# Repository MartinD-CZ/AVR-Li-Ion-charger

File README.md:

# AVR Li-Ion charger
*see the article [here](http://embedblog.eu/?p=392)*

ATtiny44-controlled buck converter with adjustable charging parameters (charging voltage & current, precharging voltage & current, min/max temperatures, ...). Everything is configurable via a serial port and stored in EEPROM.

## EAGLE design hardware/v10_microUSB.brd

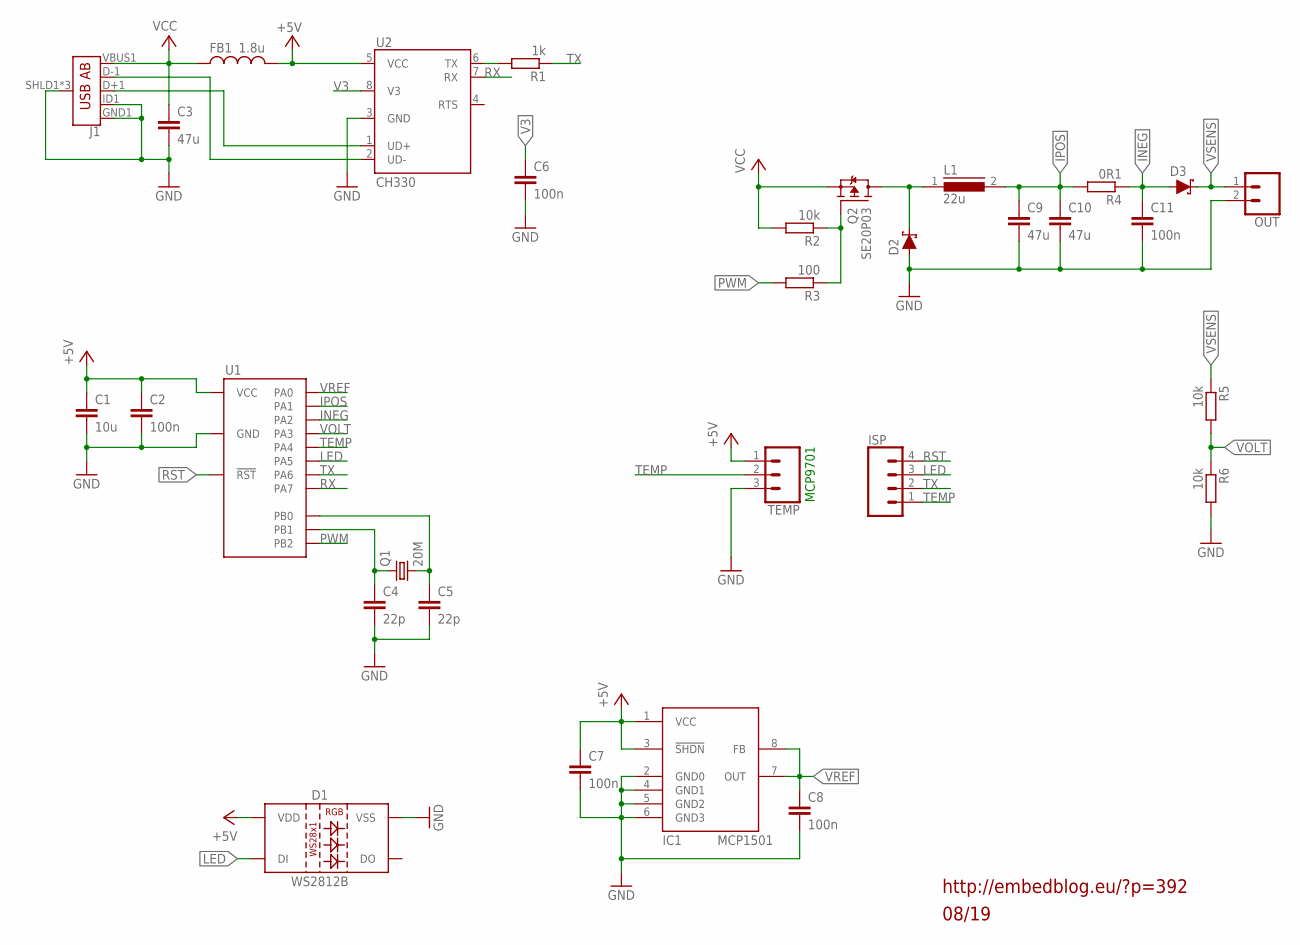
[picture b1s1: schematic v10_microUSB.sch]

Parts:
C1: 10u; C0805
C2, C6, C7, C8, C11: 100n; C0805
C3, C9, C10: 47u; C1206
C4, C5: 22p; C0805
D1: WS2812B
D2, D3: 3A/40V/500mV; SMA-DIODE
FB1: 1.8u; 1206
IC1: MCP1501; SO08
ISP: CONN_04; 1X04
J1: USB_AB_SMT; USB-AB-MICRO-SMD
L1: 22u; DR73
OUT: CONN_02PTH3; 1X02_LONGPADS
Q1: 20M; HC49/S
Q2: SE20P03; TO252
R1: 1k; R0805
R2, R5, R6: 10k; R0805
R3: 100; R0805
R4: 0R1; R1206
TEMP: 455-1750-1-ND; 1X03
U1: ATTINY24; SO014
U2: CH330; SO08

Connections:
+5V: C1.1, C2.1, C7.1, D1.1 (VDD), FB1.2, IC1.1 (VCC), IC1.3 (!SHDN), TEMP.1, U1.1 (VCC), U2.5 (VCC)
GND: C1.2, C2.2, C3.2, C4.2, C5.2, C6.2, C7.2, C8.2, C9.2, C10.2, C11.2, D1.3 (VSS), D2.A, IC1.2 (GND0), IC1.4 (GND1), IC1.5 (GND2), IC1.6 (GND3), J1.GND1 (GND), J1.ID1 (USBID), J1.SHLD1 (SHIELD), J1.SHLD2 (SHIELD), J1.SHLD3 (SHIELD), OUT.2, R6.2, TEMP.3, U1.14 (GND), U2.3 (GND)
INEG: C11.1, D3.A, R4.1, U1.11 (PA2)
IPOS: C9.1, C10.1, L1.2, R4.2, U1.12 (PA1)
LED: D1.4 (DI), ISP.3, U1.8 (PA5)
unnamed: R1.2, U2.6 (TX)
unnamed: C4.1, Q1.1, U1.3 (PB1)
unnamed: C5.1, Q1.2, U1.2 (PB0)
unnamed: Q2.1 (G), R2.1, R3.1
PWM: R3.2, U1.5 (PB2)
RST: ISP.4, U1.4 (!RST)
RX: U1.6 (PA7), U2.7 (RX)
SW: D2.C, L1.1, Q2.3 (D)
TEMP: ISP.1, TEMP.2, U1.9 (PA4)
TX: ISP.2, R1.1, U1.7 (PA6)
UD+: J1.D+1 (D+), U2.1 (UD+)
UD-: J1.D-1 (D-), U2.2 (UD-)
V3: C6.1, U2.8 (V3)
VCC: C3.1, FB1.1, J1.VBUS1 (VBUS), Q2.2 (S), R2.2
VOLT: R5.2, R6.1, U1.10 (PA3)
VREF: C8.1, IC1.7 (OUT), IC1.8 (FB), U1.13 (PA0)
VSENS: D3.C, OUT.1, R5.1

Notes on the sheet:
MCP9701
08/19
http://embedblog.eu/?p=392

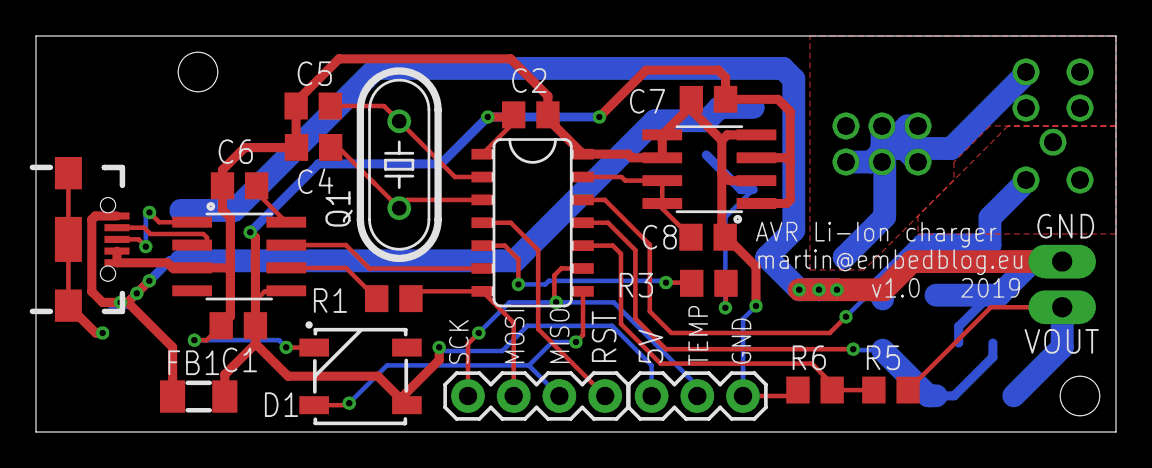
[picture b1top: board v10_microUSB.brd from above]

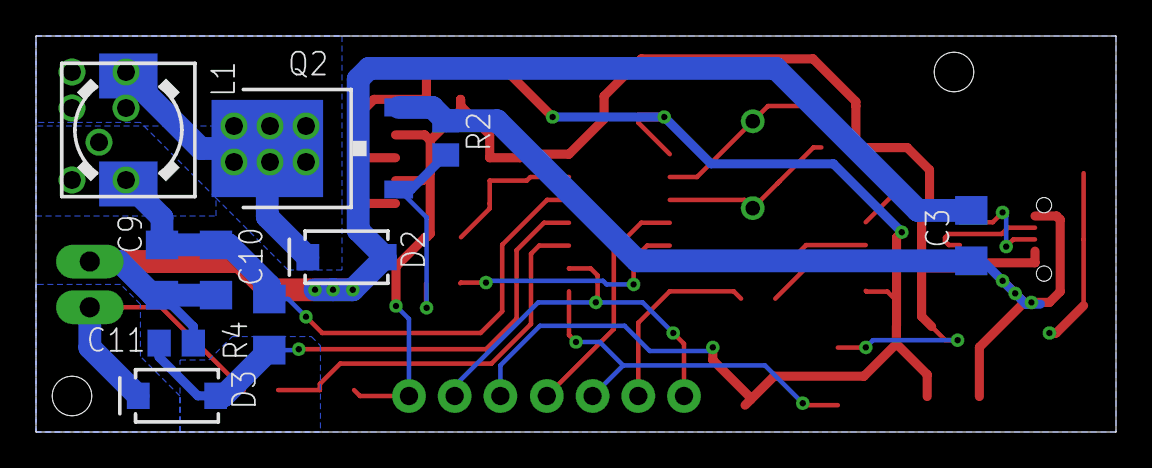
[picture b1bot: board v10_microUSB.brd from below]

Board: 2 copper layers, 60.0 x 22.0 mm, 31 parts (10 on the bottom side), 22 nets.

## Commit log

2019-08-19 V1.0 - initial
    initial release
2019-09-20 V1.0B
    added microUSB version; code optimization; layout optimization for better thermals
2019-09-28 V1.0C
    minor fixes & improvements for temperature sensor detection

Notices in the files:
parts and their libraries:
SparkFun-LED: Licensing: Creative Commons ShareAlike 4.0 International - https://creativecommons.org/licenses/by-sa/4.0
m-pad-2.1: License : GNU General Public License version 2 (see bottom)
